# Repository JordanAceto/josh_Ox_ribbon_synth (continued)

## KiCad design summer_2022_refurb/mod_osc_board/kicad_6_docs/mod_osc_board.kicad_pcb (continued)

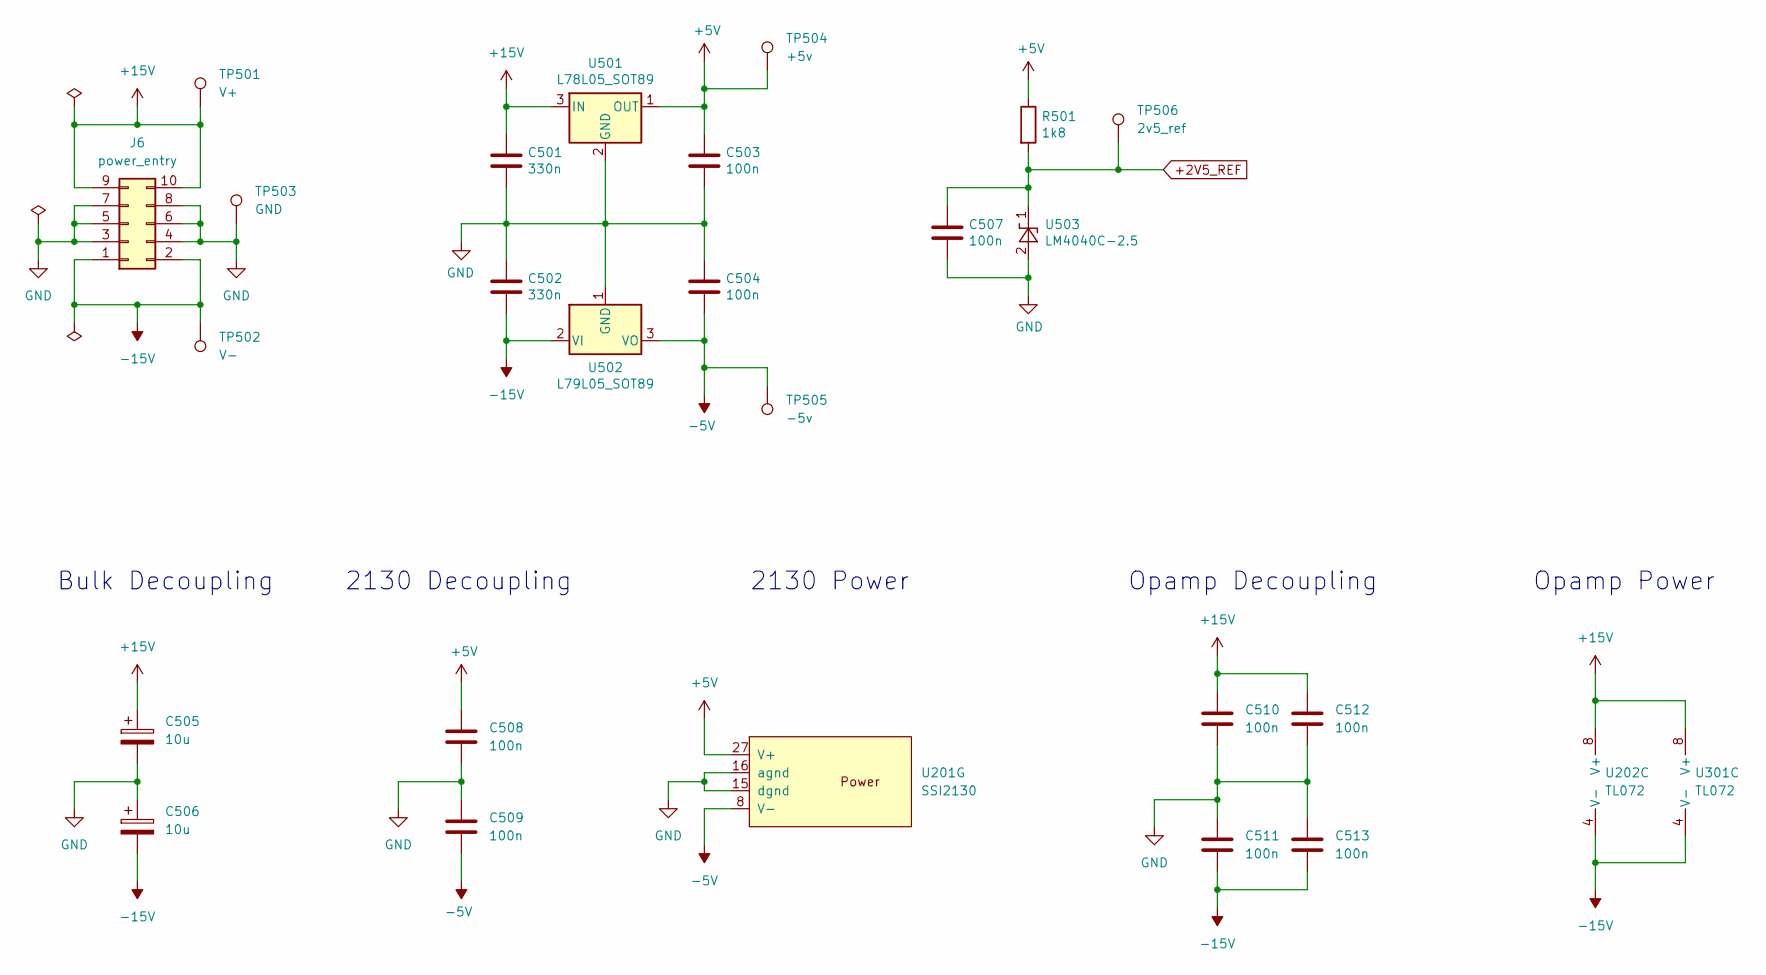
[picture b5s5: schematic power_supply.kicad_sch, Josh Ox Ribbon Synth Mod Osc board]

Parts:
C501, C502: 330n; C_0805_2012Metric
C503, C504, C507, C508, C509, C510, C511, C512, C513: 100n; C_0805_2012Metric
C505, C506: 10u; CP_Radial_D6.3mm_P2.50mm
J6: power_entry; IDC-Header_2x05_P2.54mm_Vertical
R501: 1k8; R_0805_2012Metric
TP501: V+; TestPoint_Keystone_5000-5004_Miniature
TP502: V-; TestPoint_Keystone_5000-5004_Miniature
TP503: GND; TestPoint_Bridge_Pitch7.62mm_Drill1.3mm
TP504: +5v; TestPoint_Keystone_5000-5004_Miniature
TP505: -5v; TestPoint_Keystone_5000-5004_Miniature
TP506: 2v5_ref; TestPoint_Keystone_5000-5004_Miniature
U201: SSI2130; PQN32_HandSoldering
U202, U301: TL072; SO-8_5.3x6.2mm_P1.27mm
U501: L78L05_SOT89; SOT-89-3
U502: L79L05_SOT89; SOT-89-3
U503: LM4040C-2.5; SOT-23

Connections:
+2V5_REF: C507.1, R501.2, TP506.1, U503.1 (K); also elsewhere on the board
+5V: C503.1, C508.1, R501.1, TP504.1, U201.27 (V+), U501.1 (OUT); also elsewhere on the board
+15V: C501.1, C505.1, C510.1, C512.1, J6.9, J6.10, TP501.1, U202.8 (V+), U301.8 (V+), U501.3 (IN)
-5V: C504.2, C509.2, TP505.1, U201.8 (V-), U502.3 (VO); also elsewhere on the board
-15V: C502.2, C506.2, C511.2, C513.2, J6.1, J6.2, TP502.1, U202.4 (V-), U301.4 (V-), U502.2 (VI)

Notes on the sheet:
2130 Decoupling
Opamp Decoupling
2130 Power
Opamp Power
Bulk Decoupling

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
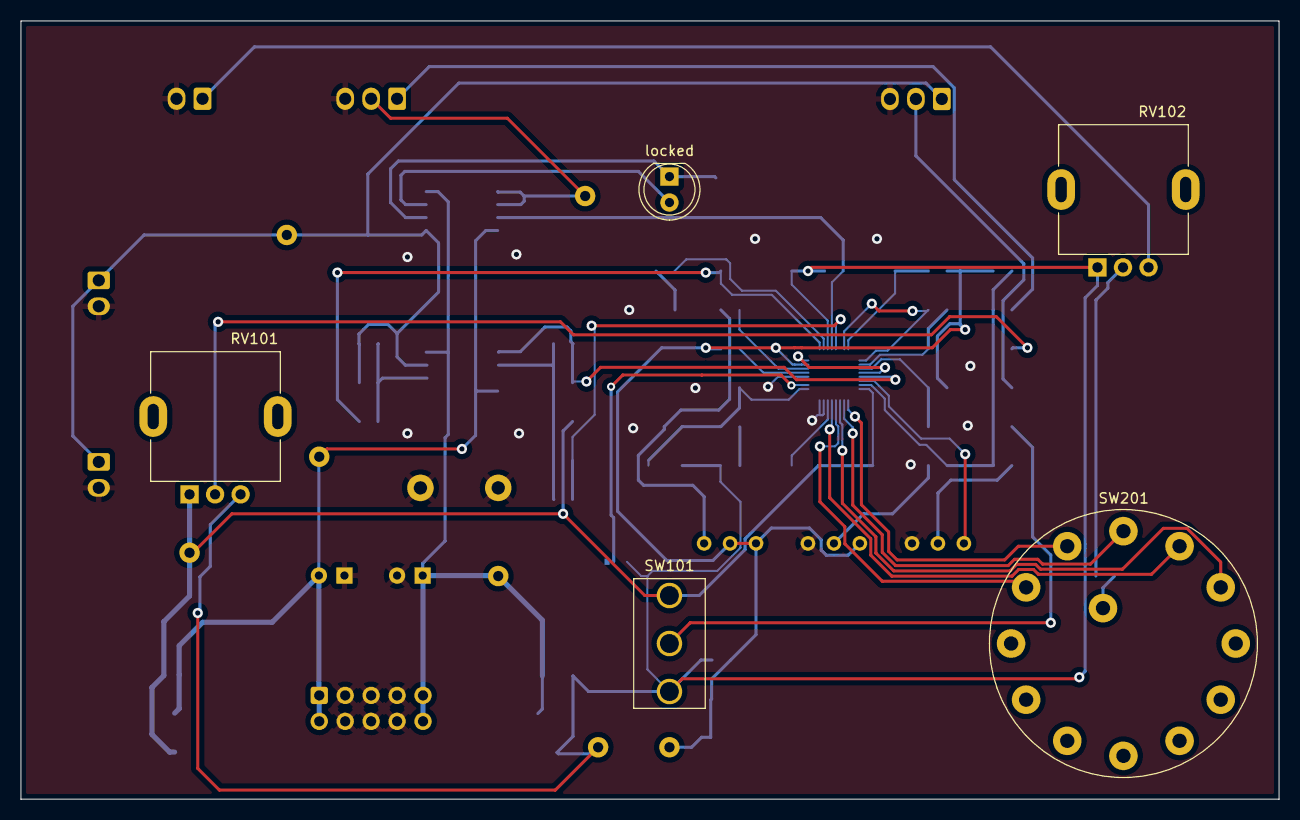
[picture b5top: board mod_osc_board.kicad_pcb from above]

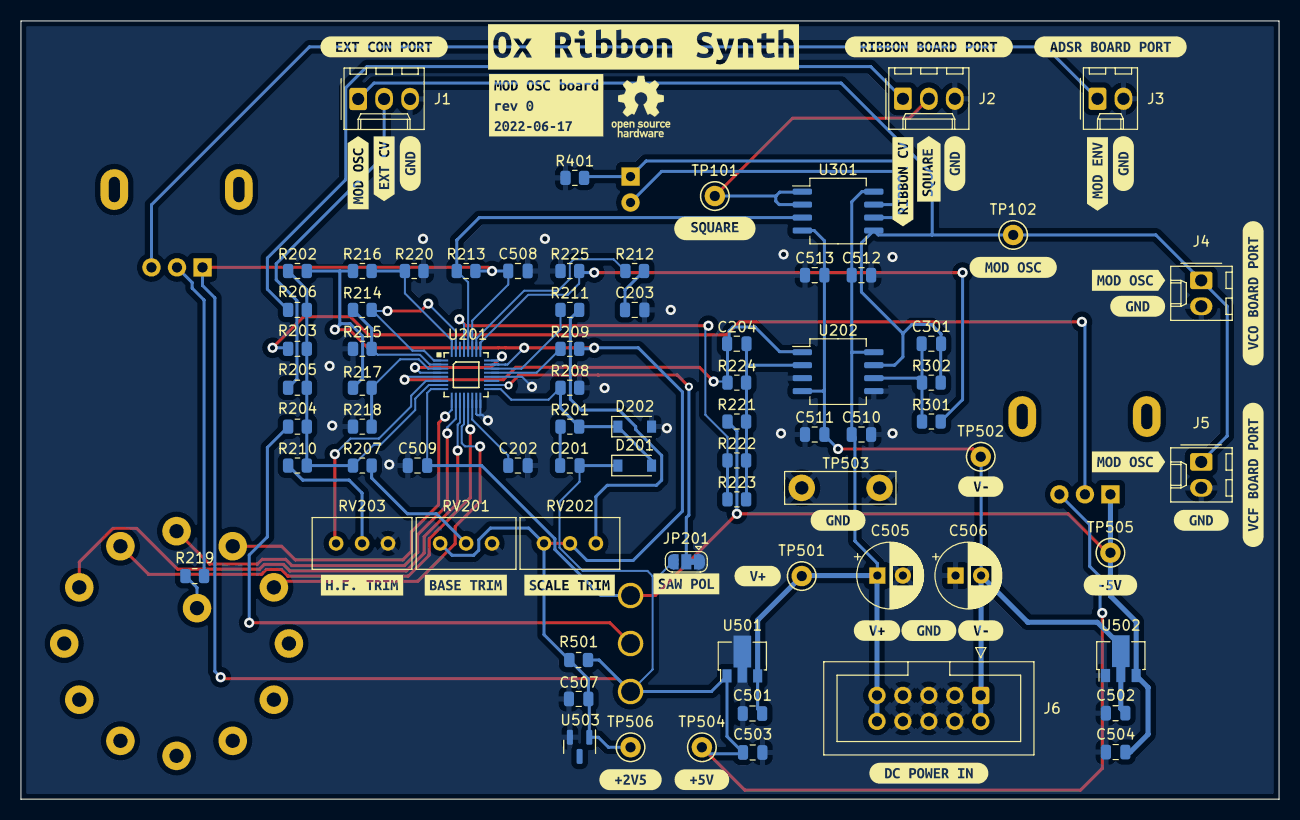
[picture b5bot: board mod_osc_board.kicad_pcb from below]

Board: 2 copper layers, 123.2 x 76.2 mm, 113 parts (108 on the bottom side), 46 nets.

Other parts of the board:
kibuzzard-62AC7A9F: G***; kibuzzard-62AC7A9F
kibuzzard-62AC7C76, kibuzzard-62AC7C76#2, kibuzzard-62AC7C76#3: G***; kibuzzard-62AC7C76
kibuzzard-62AC7CCE: G***; kibuzzard-62AC7CCE
kibuzzard-62AC7CEB: G***; kibuzzard-62AC7CEB
kibuzzard-62AC7D00: G***; kibuzzard-62AC7D00
kibuzzard-62AC7D1D: G***; kibuzzard-62AC7D1D
kibuzzard-62AC7D8B: G***; kibuzzard-62AC7D8B
kibuzzard-62AC7D30: G***; kibuzzard-62AC7D30
kibuzzard-62AC7D44: G***; kibuzzard-62AC7D44
kibuzzard-62AC7D55: G***; kibuzzard-62AC7D55
kibuzzard-62AC7D68: G***; kibuzzard-62AC7D68
kibuzzard-62AC7D79: G***; kibuzzard-62AC7D79
kibuzzard-62AC7DA9: G***; kibuzzard-62AC7DA9
kibuzzard-62AC7DB6: G***; kibuzzard-62AC7DB6
kibuzzard-62AC7DF7: G***; kibuzzard-62AC7DF7
kibuzzard-62AC7EA8: G***; kibuzzard-62AC7EA8
kibuzzard-62AC7EE1: G***; kibuzzard-62AC7EE1
kibuzzard-62AC7EFA: G***; kibuzzard-62AC7EFA
kibuzzard-62AC7F0B: G***; kibuzzard-62AC7F0B
kibuzzard-62AC78CB: G***; kibuzzard-62AC78CB
kibuzzard-62AC755C, kibuzzard-62AC755C#2, kibuzzard-62AC755C#3, kibuzzard-62AC755C#4, kibuzzard-62AC755C#5, kibuzzard-62AC755C#6, kibuzzard-62AC755C#7: G***; kibuzzard-62AC755C
kibuzzard-62AC791A, kibuzzard-62AC791A#2: G***; kibuzzard-62AC791A
kibuzzard-62AC792A, kibuzzard-62AC792A#2: G***; kibuzzard-62AC792A
kibuzzard-62AC911A: G***; kibuzzard-62AC911A
kibuzzard-62ACB089: G***; kibuzzard-62ACB089
locked: red_green; LED_D5.0mm

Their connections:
unnamed 21: locked.1 (KA); also elsewhere on the board
unnamed 22: locked.2 (AK); also elsewhere on the board
